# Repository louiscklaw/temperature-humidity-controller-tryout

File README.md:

# temperature-humidity-controller-tryout

### Design goal
1. temperature
1. humidity
1. relay control

1. hko connect
1. wifi connect
1. history

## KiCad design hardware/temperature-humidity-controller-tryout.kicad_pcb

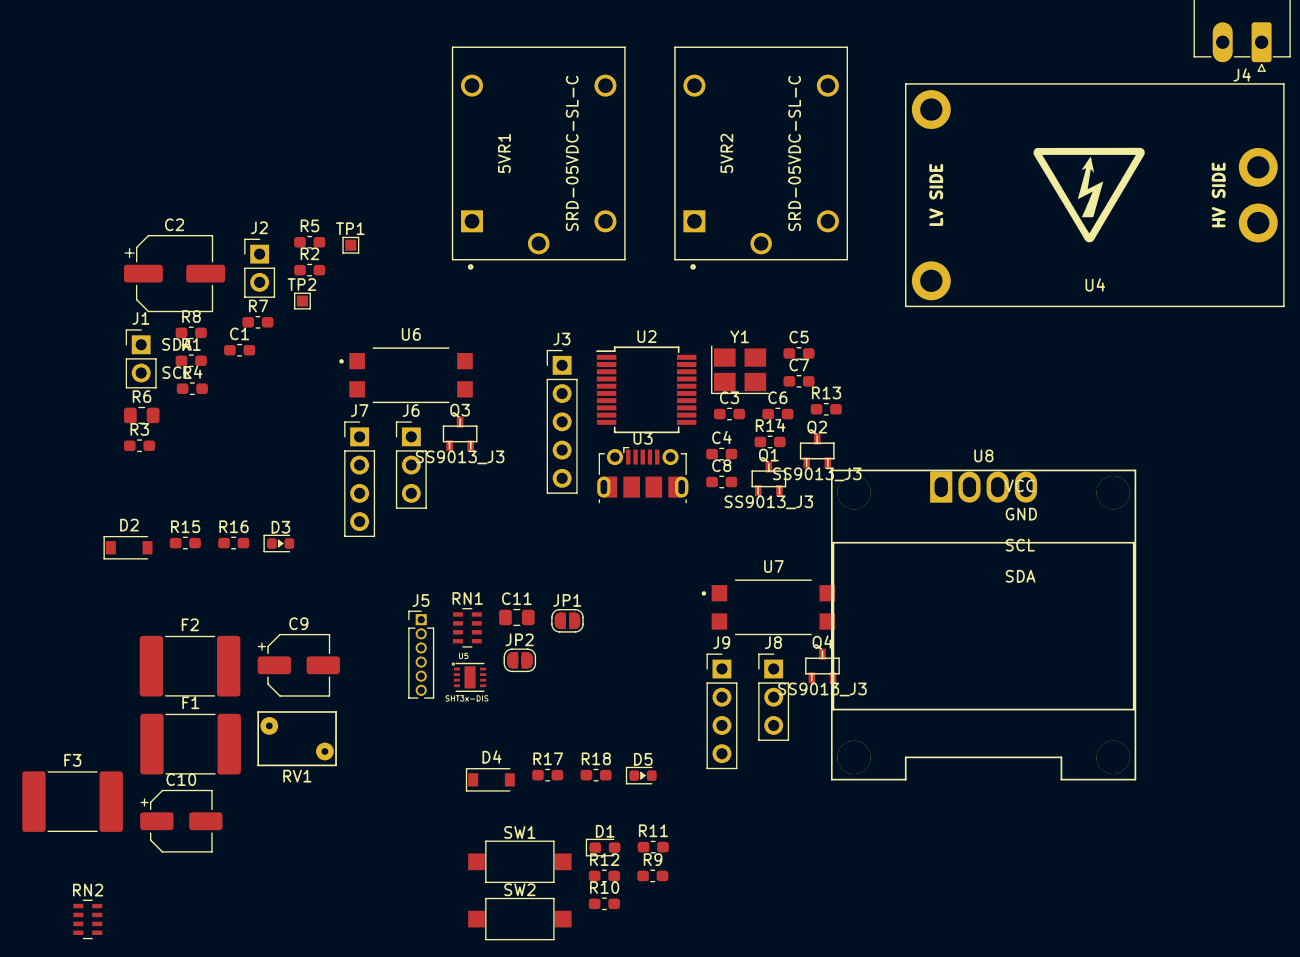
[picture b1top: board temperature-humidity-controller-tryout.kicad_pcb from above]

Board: 2 copper layers, 70 parts (1 on the bottom side), 61 nets, no tracks yet.

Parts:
5VR1, 5VR2: SRD-05VDC-SL-C
C1, C5: C104,0603; C_0603_1608Metric_Pad1.05x0.95mm_HandSolder
C2: CP100uf,10V; CP_Elec_6.3x5.3
C3: C475,0603; C_0603_1608Metric_Pad1.05x0.95mm_HandSolder
C4: C225,0603; C_0603_1608Metric_Pad1.05x0.95mm_HandSolder
C6: C103,0603; C_0603_1608Metric_Pad1.05x0.95mm_HandSolder
C7, C8: C22pf,0603; C_0603_1608Metric_Pad1.05x0.95mm_HandSolder
C9: CP10uf,50V; CP_Elec_5x5.3
C10: CP22uf,25V; CP_Elec_5x5.3
C11: C104,0805; C_0805_2012Metric_Pad1.15x1.40mm_HandSolder
D1: LED_BLUE,0603; LED_0603_1608Metric_Pad1.05x0.95mm_HandSolder
D2, D4: D_1N4148_T4; D_SOD-123
D3, D5: LED_RED,0603; LED_0603_1608Metric
F1, F2, F3: Fuse_Small; Fuse_2920_7451Metric_Pad2.10x5.45mm_HandSolder
J1: I2C_HEADER,2.54; I2C_DEBUG,2.54
J2: DEBUG_HEADER; PinHeader_1x02_P2.54mm_Vertical
J3: USB_DBG; PinHeader_1x05_P2.54mm_Vertical
J4: HV_IN; PhoenixContact_MC_1,5_2-G-3.5_1x02_P3.50mm_Horizontal
J5: SHT3x_HEADER; PinHeader_1x06_P1.27mm_Vertical
J6, J8: RELAY_OUT_HEADER; PinHeader_1x03_P2.54mm_Vertical
J7, J9: RELAY_HEADER; PinHeader_1x04_P2.54mm_Vertical
JP1: SolderJumper_2_Open_round; SolderJumper-2_P1.3mm_Open_RoundedPad1.0x1.5mm
JP2: J_ADDR; SolderJumper-2_P1.3mm_Open_RoundedPad1.0x1.5mm
Q1, Q2, Q3, Q4: SS9013_J3; 9013,J3,SOT23
R1, R9, R10, R12: R471,0603; R_0603_1608Metric_Pad1.05x0.95mm_HandSolder
R2, R3, R4, R5, R7, R13, R14: R123,0603; R_0603_1608Metric_Pad1.05x0.95mm_HandSolder
R6: R224,0805; R_0805_2012Metric_Pad1.15x1.40mm_HandSolder
R8: R104,0603; R_0603_1608Metric_Pad1.05x0.95mm_HandSolder
R11: R0,0603; R_0603_1608Metric_Pad1.05x0.95mm_HandSolder
R15, R17: R102,0603; R_0603_1608Metric_Pad1.05x0.95mm_HandSolder
R16, R18: R511,0603; R_0603_1608Metric_Pad1.05x0.95mm_HandSolder
RN1, RN2: RN_472,0603; R_Array_Concave_4x0603
RV1: Varistor; RV_Disc_D7mm_W4.8mm_P5mm
SW1: FLASH_BUTTON; SW_SPST_CK_RS282G05A3
SW2: SW_RESET,2_leg,SMD; SW_SPST_CK_RS282G05A3
TP1: TP_RXD; TestPoint_Pad_1.0x1.0mm
TP2: TP_TXD; TestPoint_Pad_1.0x1.0mm
U1: ESP12; ESP-12E
U2: CH340T; CH340T_SSOP-20
U3: USB_Micro; USB_Micro-B_Molex-105017-0001
U4: HLK-PM03
U5: SHT3x-DIS
U6, U7: EL817S1
U8: SSD1306-OLED-I2C; OLED_096_12864_SSD1306_LOW
Y1: O_12M,3225; OSC_3225

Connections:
+3V3: C2.1, C9.1, C10.1, C11.2, F1.2, J5.2, J7.3, J9.3, JP1.1, R2.2, R3.2, R4.2, R5.2, R9.1, R15.1, R17.1, RN1.5, RN1.6, RN2.5, RN2.6, RN2.7, RN2.8, U1.8, U5.5, U8.VCC
+5V: 5VR1.A1, 5VR2.A1, C3.2, C4.1, C5.1, D2.1, D4.1, J7.2, J9.2, U2.19, U6.4, U7.4
/ESP-12/ADC: R6.2, R8.1, U1.2
/ESP-12/EN: R4.1, U1.3
/ESP-12/GPIO0: Q2.3, R2.1, R10.1, U1.18
/ESP-12/GPIO2: J2.2, R3.1, U1.17
/ESP-12/GPIO15: R7.2, U1.16
/ESP-12/GPIO16: D1.1, R11.1, U1.4
/ESP-12/RXD: R1.2, TP1.1, U1.21
/ESP-12/SCL: J1.SCL, U1.20
/ESP-12/SDA: J1.SDA, U1.19
/ESP-12/TXD: TP2.1, U1.22, U2.3
/ESP-12/nRST: C1.1, Q1.3, R5.1, R12.1, U1.1
/ESP-12/usb_to_uart/DTR: Q2.2, R13.1, U2.15
/ESP-12/usb_to_uart/ID: J3.4, U3.4
/ESP-12/usb_to_uart/RTS: Q1.2, R14.1, U2.16
/ESP-12/usb_to_uart/RXD0: R1.1, U2.4
/ESP-12/usb_to_uart/USB_N: J3.2, U2.7, U3.2
/ESP-12/usb_to_uart/USB_P: J3.3, U2.6, U3.3
/relay1/COM1: 5VR1.COM, J6.1
/relay1/IN1: D3.1, J7.4
/relay1/NC1: 5VR1.NC, J6.2
/relay1/NO1: 5VR1.NO, J6.3
/relay2/COM1: 5VR2.COM, J8.1
/relay2/IN1: D5.1, J9.4
/relay2/NC1: 5VR2.NC, J8.2
/relay2/NO1: 5VR2.NO, J8.3
/sensor/ADDR: JP2.1, RN1.3, U5.2
/sensor/ALERT: J5.5, U5.3
/sensor/NRST: J5.6, RN1.4, U5.6
/sensor/SCL: J5.4, RN1.2, U5.4
/sensor/SDA: J5.3, RN1.1, U5.1
/ssd1306/SCL: RN2.2, U8.SCL
/ssd1306/SDA: RN2.1, U8.SDA
GND: C1.2, C2.2, C3.1, C4.2, C5.2, C6.2, C7.2, C8.2, C11.1, J2.1, J3.5, J5.1, J7.1, J9.1, JP2.2, Q3.2, Q4.2, R7.1, R8.2, SW1.2, SW2.2, U1.15, U2.8, U3.5, U3.6, U3.7, U3.8, U3.9, U5.7, U5.8, U5.PAD, U8.GND, Y1.2
unnamed: 5VR1.A2, D2.2, Q3.3
unnamed: 5VR2.A2, D4.2, Q4.3
unnamed: C6.1, U2.5
unnamed: C7.1, U2.9, Y1.3
unnamed: C8.1, U2.10, Y1.1
unnamed: C9.2, C10.2, U4.3
unnamed: D1.2, R9.2
unnamed: D3.2, U6.2
unnamed: D5.2, U7.2
unnamed: F1.1, U4.4
unnamed: F2.1, RV1.2, U4.2
unnamed: F2.2, F3.1
unnamed: F3.2, J4.1
unnamed: J4.2, RV1.1, U4.1
unnamed: JP1.2, RN1.7, RN1.8
unnamed: Q1.1, R13.2
unnamed: Q2.1, R14.2
unnamed: Q3.1, R16.1
unnamed: Q4.1, R18.1
unnamed: R10.2, SW1.1
unnamed: R11.2, R12.2, SW2.1
unnamed: R15.2, U6.1
unnamed: R16.2, U6.3
unnamed: R17.2, U7.1
unnamed: R18.2, U7.3
VBUS: J3.1, U3.1

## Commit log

2019-07-04 init commit,
2019-07-04 update,
2020-05-05 ci: init travis build config,
2020-05-05 ci: init travis token,
